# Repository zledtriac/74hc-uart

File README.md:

# 74hc-uart
In this project, you can find a schematics and descriptions for an asynchronous serial transmitter and receiver with 74hcxxx ICs. The circuits can be used for diy and old cpus where there is no support for UART, or you can just check the schematics to get an idea how an UART could be implemented in microcontrollers. It could be useful for VHDL designs.

## Transmitter
You can find the schematics and a detailed description of the serial transmitter in the ./hardware/transmitter folder.

## Receiver
Coming soon!

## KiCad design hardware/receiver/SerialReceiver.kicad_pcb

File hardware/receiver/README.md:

# Receiver
This is the receiver. It's only consists of 6 ICs. Actually 5 because U6 the 74HC244 IC can be left out, but with the current configuration it can 
be operated manually for demonstrations.

The receiver can receive a serial data transmission with **1 start bit, 8bit data without parity and 1 stop bit** on the end, with 9600 baude rate.

## Operation
The receiver has 3 pin headers for selecting the mode of operation (J4, J5, J6), before powering the receiver up, **please check the jumper positions, 
because the receiver can't operate in a circuit if the receiver is in manual operation mode.**

The receiver needs a 5V power supply to work, the power pins can be found on the Control header (J2) pin 1 - VCC, pin 2 - GND. After powering up the
receiver, due to the random behaviour of the U5A and U5B (74HC74) D flip-flops, it is possible that the cicuit will load a random data in the output 
register. It is recommanded to wait one full transmition time after power up and read the output register in order to clear the data ready signaling 
U5B D flip-flop.

The Control header (J2) has two other pins for control, pin 4 - !RD, and pin 7 - Ready. The !RD is an active-low input and this input enables the 
output shift register's tri-state output drivers so the received data will be present on the output.
The Ready is an output which will turns on when the data is received and ready to read.

When the RX input goes low, it will start the colock divider and if the input is held low for more than half the time of one bit then U5B (74HC74) 
D flip-flop will be set, and the Input trigger will lock on the signal and keeps the clock divider running. When the clock divider is running it means 
that the Bit counter and the Output shift register will receive a clock signal, and the data reception sequence is in progress. When the Q3 output on 
the Bit counter goes high, it will stops the Clock divider and the circuit will wait until the RX input goes back to high, and when the RX input went 
high it will resets the Input trigger and load the received data into the U4 (74HC595) output register and sets the U5A (74HC74) D flip-flop so the 
Ready output will turn to high.

The Output data register can be read at the same time when the data reception sequence is running because the output data register only updates when 
the data reception sequence is finished. But if the data is not readed befor the second reception finishes it will overwrite the data in the output 
register so the previous data will be lost.

## Manual operation
To use the circuit in a manual operation mode, set the jumper on the J5 pin header to enable the output of the U6 (74HC244) IC so the data on the 
output can be seen on the LED bar. If you want to use the button as a read signal then bridge the 1-2 pins on the J6 Mode select pin header. Or if you 
want to see the received data immediatelly, bridge the 3-4 pins in the J6 Mode select pin header.

## Oscillator
The oscillator is made out of two schmitt-triggered NAND gate of the U1 (74HC132) IC. With the 560pF C1 capacitor and the 10kOhm R1 plus the 10kOhm RV1 trimmer 
potentiometer this oscillator can be adjusted between 107kHz and 214kHz. The oscillator's frequency is not equal to the baud rate, because the sampling clock is
generated with the U2 (74HC191) counter IC which is in this case act as a clock divider. The Q3 output of the U2 (74HC191) IC will give a square wave signal with 
16th of the input frequency. So the equation for the baudrate is:
```
baud_rate = input_freq / 16
```
So the frequency of the oscillator should be 153.6kHz for a 9600 baud rate.\
For tuning the oscillator, a simple digital multimeter with frequency measuring capability is enough.

The J4 Clock select pin header can be used to fed external clock signal into the circuit. Just unplug the bridge from the 2-3 pins and connect the external clock 
signal the pin 3. The pin 4 can be used as a grounding point.

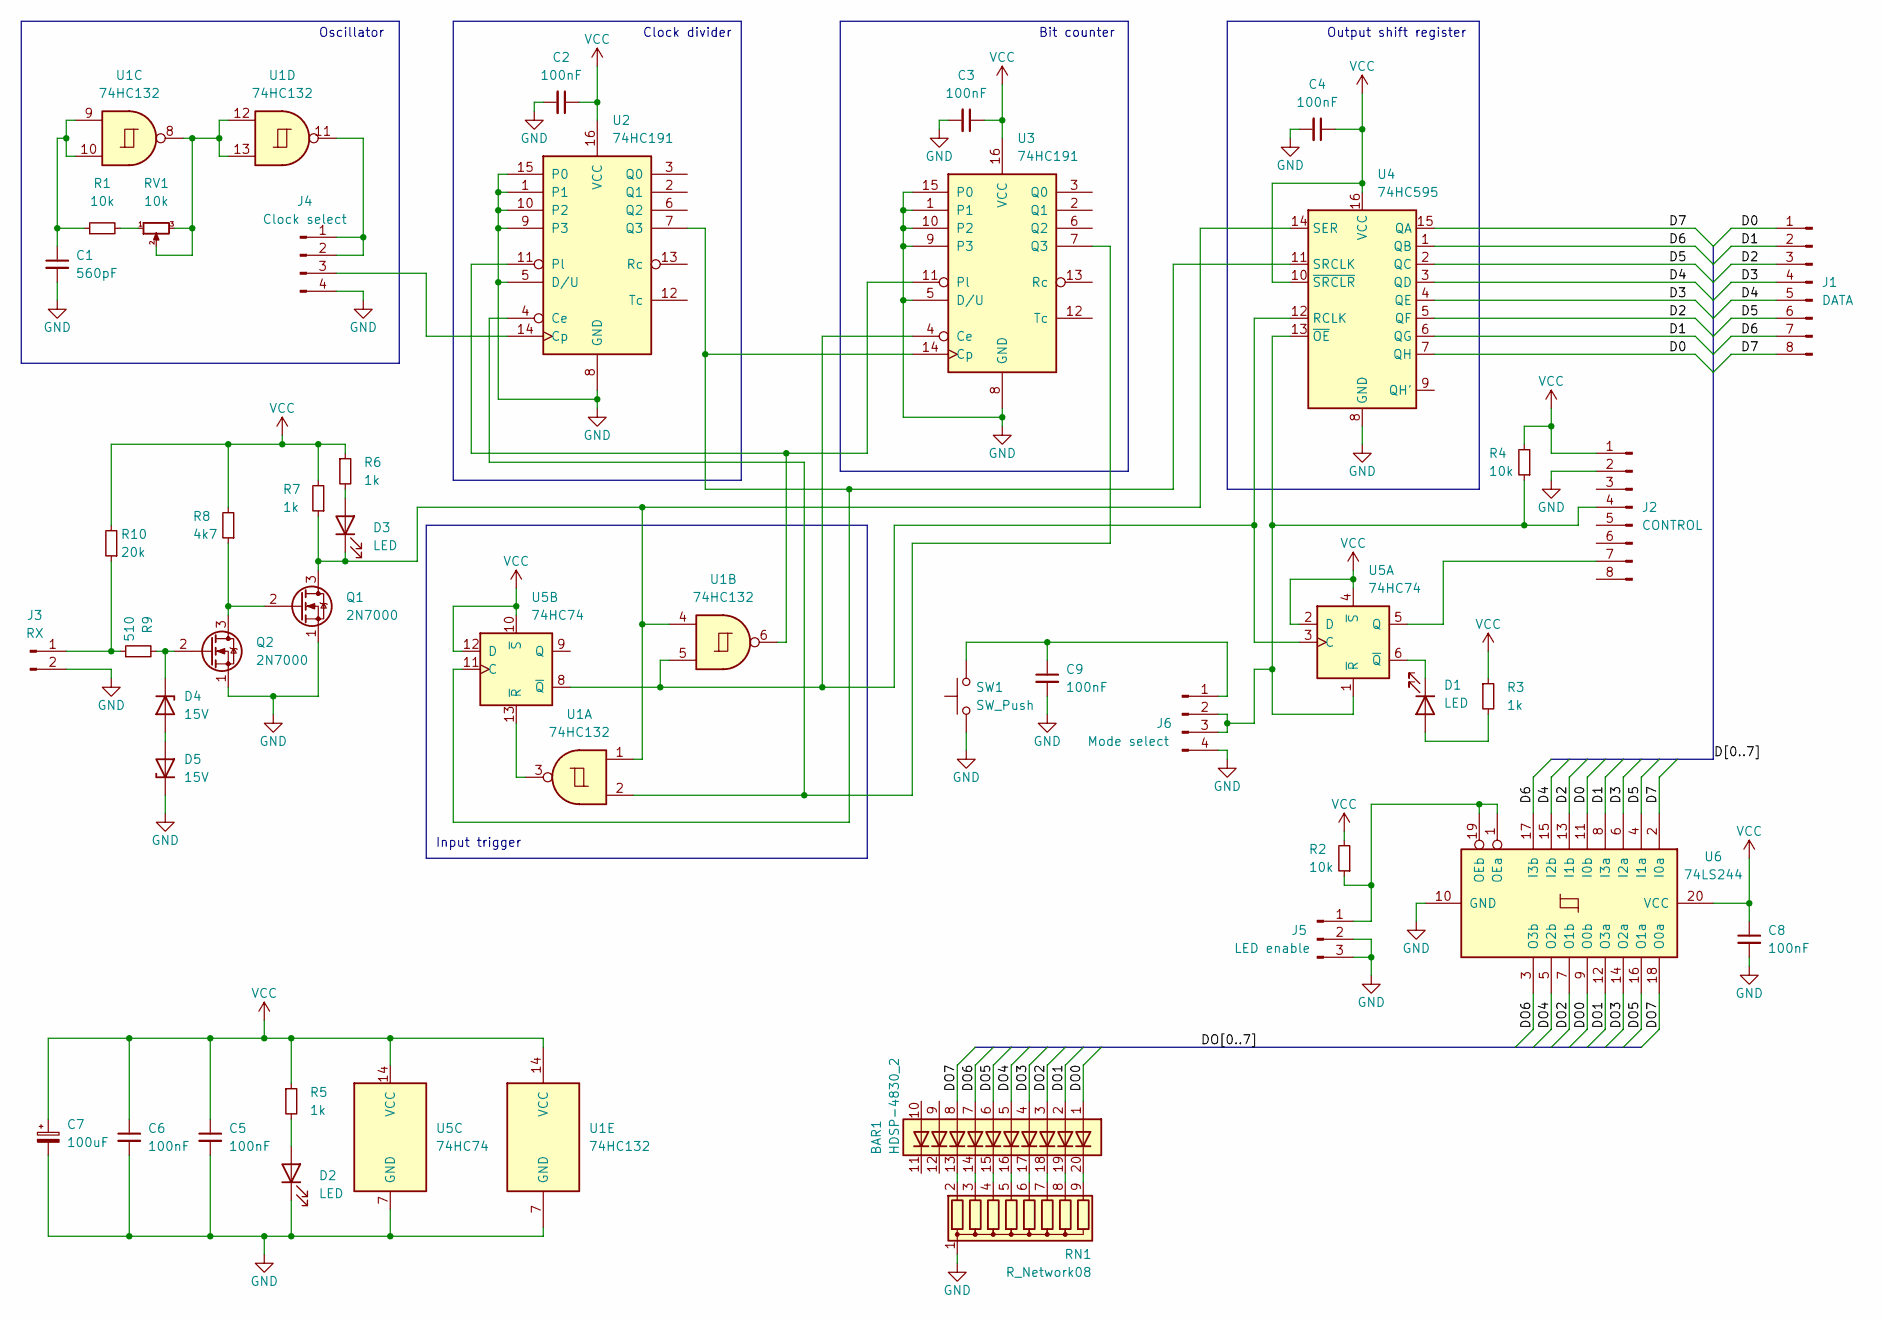
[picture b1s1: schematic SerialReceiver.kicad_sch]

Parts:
BAR1: HDSP-4830_2; DIP-20_W7.62mm_Socket
C1: 560pF; C_Disc_D3.0mm_W2.0mm_P2.50mm
C2, C3, C4, C5, C6, C8, C9: 100nF; C_Disc_D3.0mm_W2.0mm_P2.50mm
C7: 100uF; CP_Radial_D6.3mm_P2.50mm
D1, D2, D3: LED; LED_D3.0mm
D4, D5: 15V; D_DO-35_SOD27_P7.62mm_Horizontal
J1: DATA; PinHeader_1x08_P2.54mm_Horizontal
J2: CONTROL; PinHeader_1x08_P2.54mm_Horizontal
J3: RX; PinHeader_1x02_P2.54mm_Horizontal
J4: Clock select; PinHeader_1x04_P2.54mm_Vertical
J5: LED enable; PinHeader_1x03_P2.54mm_Vertical
J6: Mode select; PinHeader_1x04_P2.54mm_Vertical
Q1, Q2: 2N7000; TO-92_Inline_Wide
R1, R2, R4: 10k; R_Axial_DIN0207_L6.3mm_D2.5mm_P10.16mm_Horizontal
R3, R5, R6, R7: 1k; R_Axial_DIN0207_L6.3mm_D2.5mm_P10.16mm_Horizontal
R8: 4k7; R_Axial_DIN0207_L6.3mm_D2.5mm_P10.16mm_Horizontal
R9: 510; R_Axial_DIN0207_L6.3mm_D2.5mm_P10.16mm_Horizontal
R10: 20k; R_Axial_DIN0207_L6.3mm_D2.5mm_P10.16mm_Horizontal
RN1: R_Network08; R_Array_SIP9
RV1: 10k; Potentiometer_Bourns_3296W_Vertical
SW1: SW_Push; SW_PUSH_6mm
U1: 74HC132; DIP-14_W7.62mm
U2, U3: 74HC191; DIP-16_W7.62mm
U4: 74HC595; DIP-16_W7.62mm
U5: 74HC74; DIP-14_W7.62mm
U6: 74LS244; DIP-20_W7.62mm

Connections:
/D0: J1.1, U4.7 (QH), U6.11 (I0b)
/D1: J1.2, U4.6 (QG), U6.8 (I3a)
/D2: J1.3, U4.5 (QF), U6.13 (I1b)
/D3: J1.4, U4.4 (QE), U6.6 (I2a)
/D4: J1.5, U4.3 (QD), U6.15 (I2b)
/D5: J1.6, U4.2 (QC), U6.4 (I1a)
/D6: J1.7, U4.1 (QB), U6.17 (I3b)
/D7: J1.8, U4.15 (QA), U6.2 (I0a)
/DO0: BAR1.1 (A), U6.9 (O0b)
/DO1: BAR1.2 (A), U6.12 (O3a)
/DO2: BAR1.3 (A), U6.7 (O1b)
/DO3: BAR1.4 (A), U6.14 (O2a)
/DO4: BAR1.5 (A), U6.5 (O2b)
/DO5: BAR1.6 (A), U6.16 (O1a)
/DO6: BAR1.7 (A), U6.3 (O3b)
/DO7: BAR1.8 (A), U6.18 (O0a)
GND: C1.2, C2.2, C3.2, C4.2, C5.2, C6.2, C7.2, C8.2, C9.2, D2.1 (K), D5.1 (K), J2.2, J3.2, J4.4, J5.2, J5.3, J6.4, Q1.1 (S), Q2.1 (S), RN1.1 (common), SW1.1, U1.7 (GND), U2.1, U2.5 (D/U), U2.8 (GND), U2.9 (P3), U2.10 (P2), U2.15 (P0), U3.1, U3.5 (D/U), U3.8 (GND), U3.9 (P3), U3.10 (P2), U3.15 (P0), U4.8 (GND), U5.7 (GND), U6.10 (GND)
unnamed: BAR1.13 (K), RN1.2 (R1)
unnamed: BAR1.14 (K), RN1.3 (R2)
unnamed: BAR1.15 (K), RN1.4 (R3)
unnamed: BAR1.16 (K), RN1.5 (R4)
unnamed: BAR1.17 (K), RN1.6 (R5)
unnamed: BAR1.18 (K), RN1.7 (R6)
unnamed: BAR1.19 (K), RN1.8 (R7)
unnamed: BAR1.20 (K), RN1.9 (R8)
unnamed: C1.1, R1.1, U1.9, U1.10
unnamed: C9.1, J6.1, SW1.2
unnamed: D1.1 (K), U5.6 (~Q)
unnamed: D1.2 (A), R3.2
unnamed: D2.2 (A), R5.2
unnamed: D3.1 (K), Q1.3 (D), R7.1, U1.1, U1.4, U4.14 (SER)
unnamed: D3.2 (A), R6.2
unnamed: D4.1 (K), Q2.2 (G), R9.2
unnamed: D4.2 (A), D5.2 (A)
unnamed: J2.4, J6.2, J6.3, R4.1, U4.13 (~OE), U5.1 (~R)
unnamed: J2.7, U5.5 (Q)
unnamed: J3.1, R9.1, R10.1
unnamed: J4.1, J4.2, U1.11
unnamed: J4.3, U2.14 (Cp)
unnamed: J5.1, R2.1, U6.1 (OEa), U6.19 (OEb)
unnamed: Q1.2 (G), Q2.3 (D), R8.1
unnamed: R1.2, RV1.1
unnamed: U1.2, U2.4 (Ce), U3.7 (Q3)
unnamed: U1.3, U5.13 (~R)
unnamed: U1.5, U3.4 (Ce), U4.12 (RCLK), U5.3 (C), U5.8 (~Q)
unnamed: U1.6, U2.11 (Pl), U3.11 (Pl)
unnamed: RV1.2, RV1.3, U1.8, U1.12, U1.13
unnamed: U2.7 (Q3), U3.14 (Cp), U4.11 (SRCLK), U5.11 (C)
VCC: C2.1, C3.1, C4.1, C5.1, C6.1, C7.1, C8.1, J2.1, R2.2, R3.1, R4.2, R5.1, R6.1, R7.2, R8.2, R10.2, U1.14 (VCC), U2.16 (VCC), U3.16 (VCC), U4.10 (~SRCLR), U4.16 (VCC), U5.2 (D), U5.4 (~S), U5.10 (~S), U5.12 (D), U5.14 (VCC), U6.20 (VCC)

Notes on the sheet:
Bit counter
Clock divider
Oscillator
Output shift register
Input trigger

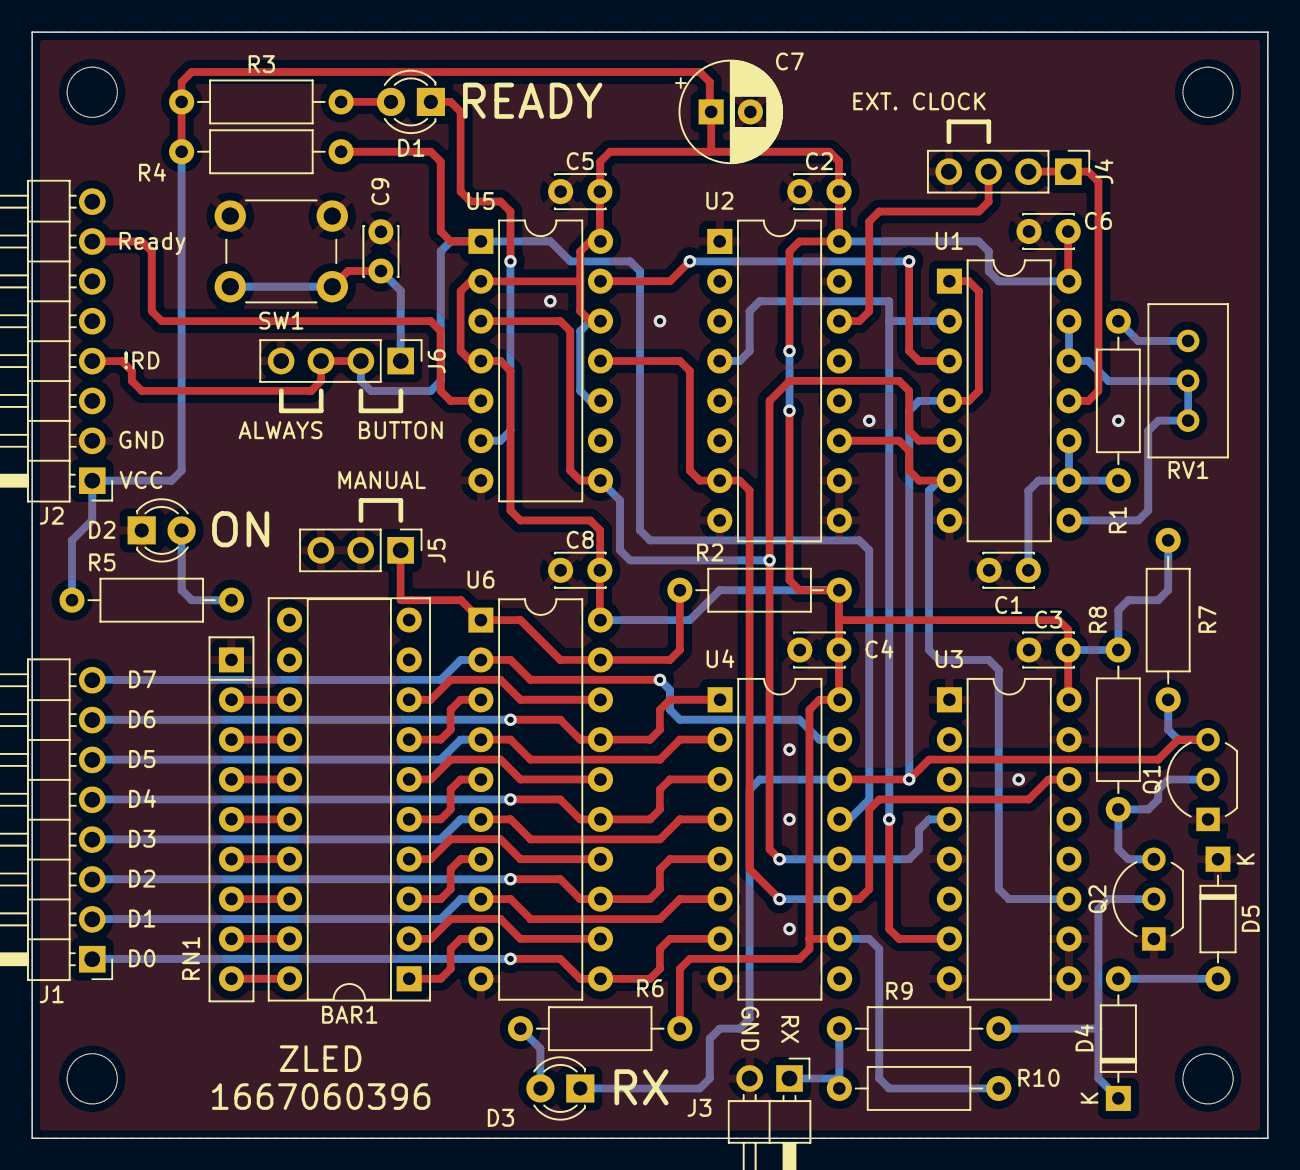
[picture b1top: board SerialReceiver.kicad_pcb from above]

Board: 2 copper layers, 78.7 x 70.5 mm, 42 parts (0 on the bottom side), 49 nets.

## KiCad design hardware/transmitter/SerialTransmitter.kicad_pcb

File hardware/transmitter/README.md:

# Transmitter
This is the transmitter. It's only consists of 6 ICs. Actually 5 because U6 the 74HC244 IC can be left out, but with the current configuration it can 
be operated manually for demonstrations.

The transmitter transmits the data with **1 start bit, 8bit data without parity and 1 stop bit** on the end, with 9600 baud rate.

## Operation
The transmitter has 3 pin headers for selecting the mode of operation (J3, J5, J6), before powering the transmitter up, **please check the jumper positions, 
because the transmitter can't operate in a circuit if the transmitter is in manual operation mode.**

The transmitter needs a 5V power supply to work, the power pins can be found on the Control header (J4) pin 1 - VCC, pin 2 - GND. After powering up the
transmitter, due to the random behaviour of the set-reset latch made with the U5D and U5C NAND gate (74HC132) and of the U3A and U3B (74HC74) D flip-flops, 
it is possible that the cicuit will transmit a random data on the output.

*If this behaviour can cause issues in the target device, it is recommended to build
an output enable circuit after the U3B pin 9 output, which can be controlled by a switch, delay circuit or from software if the transmitter is connected to a CPU.*

The Control header (J4) has two other pins for control, pin 5 - !WR, and pin 8 - Busy. The !WR is an active-low input and this input starts the data transmission.
The Busy is an output which will be held high while the transmission is going (Short pulse section on *Figure 1.*), or while the !WR input is held low (Long pulse section on *Figure 1.*).

To send data, first set the data on the Data header (J1) then send a low pulse on the !WR pin. This will trigger the Input trigger circuitry. In this stage the output 
of the U5D will turn high, but since the U3A D flip-flop is not set, the inverted output of the U3A D flip-flop is also high, this will set the output of the U4A NAND 
gate to low, this will enables the load pins of the U1 (74HC165) shift register and the U2 (74HC191) counter IC, so the data will be loaded into the U1 shift register 
and the U2 counter IC will be set to 0. There is an extra bit made by the U4B NAND gate and the U3B D flip-flop, in the loading process it will set to one, this extra 
bit is the START bit. Since the U3A D flip-flop's clock input is connected to the main clock signal, the U3A D flip-flop will set and the inverted output of the U3A D 
flip-flop will turn to low.
After this, every clock pulse will shift out the data from U1 (74HC165) shift register, and increment the U2 (74HC191) counter until U2 (74HC191) counter reaches 8.
When the U2 (74HC191) counter reaches 8, the counting will stop and if the !WR input is high, it will reset the Input trigger circuitry, and after this, one clock 
pulse is needed to reset the U3A D flip-flop. So when the next write pulse comes in, the whole process will repeat.

## Manual operation
To use the circuit in a manual operation mode, set the jumper on the J3 pin header to bridge the 1-2 pins, and on the J5 pin header to bridge the 2-3 pins. This will 
enables the U6 (74HC244) output so the data set by the SW1 dip switch will be put on the DATA input, and it will connect the SW2 button to the !WR input.
After the data set on the SW1 dip switch, the data sending can be initiated by pressing the SW2 button.

**please note that if the circuit is in manual operation mode, the DATA input will be driven by the U6 (74HC244) output and the !WR input will connected to the SW2 
button, so it can't be used in other circuits!**

## Oscillator
The oscillator is made out of two schmitt-triggered NAND gate of the U4 (74HC132) IC. With the 10nF C7 capacitor and the 10kOhm R5 plus the 10kOhm RV1 trimmer 
potentiometer this oscillator can be adjusted between 6kHz and 12kHz. The oscillator's frequency is equal to the baud rate, so for the 9600 baud rate set the 
oscillator to 9.6kHz. For the tuning, a simple digital multimeter with frequency measuring capability is enough.

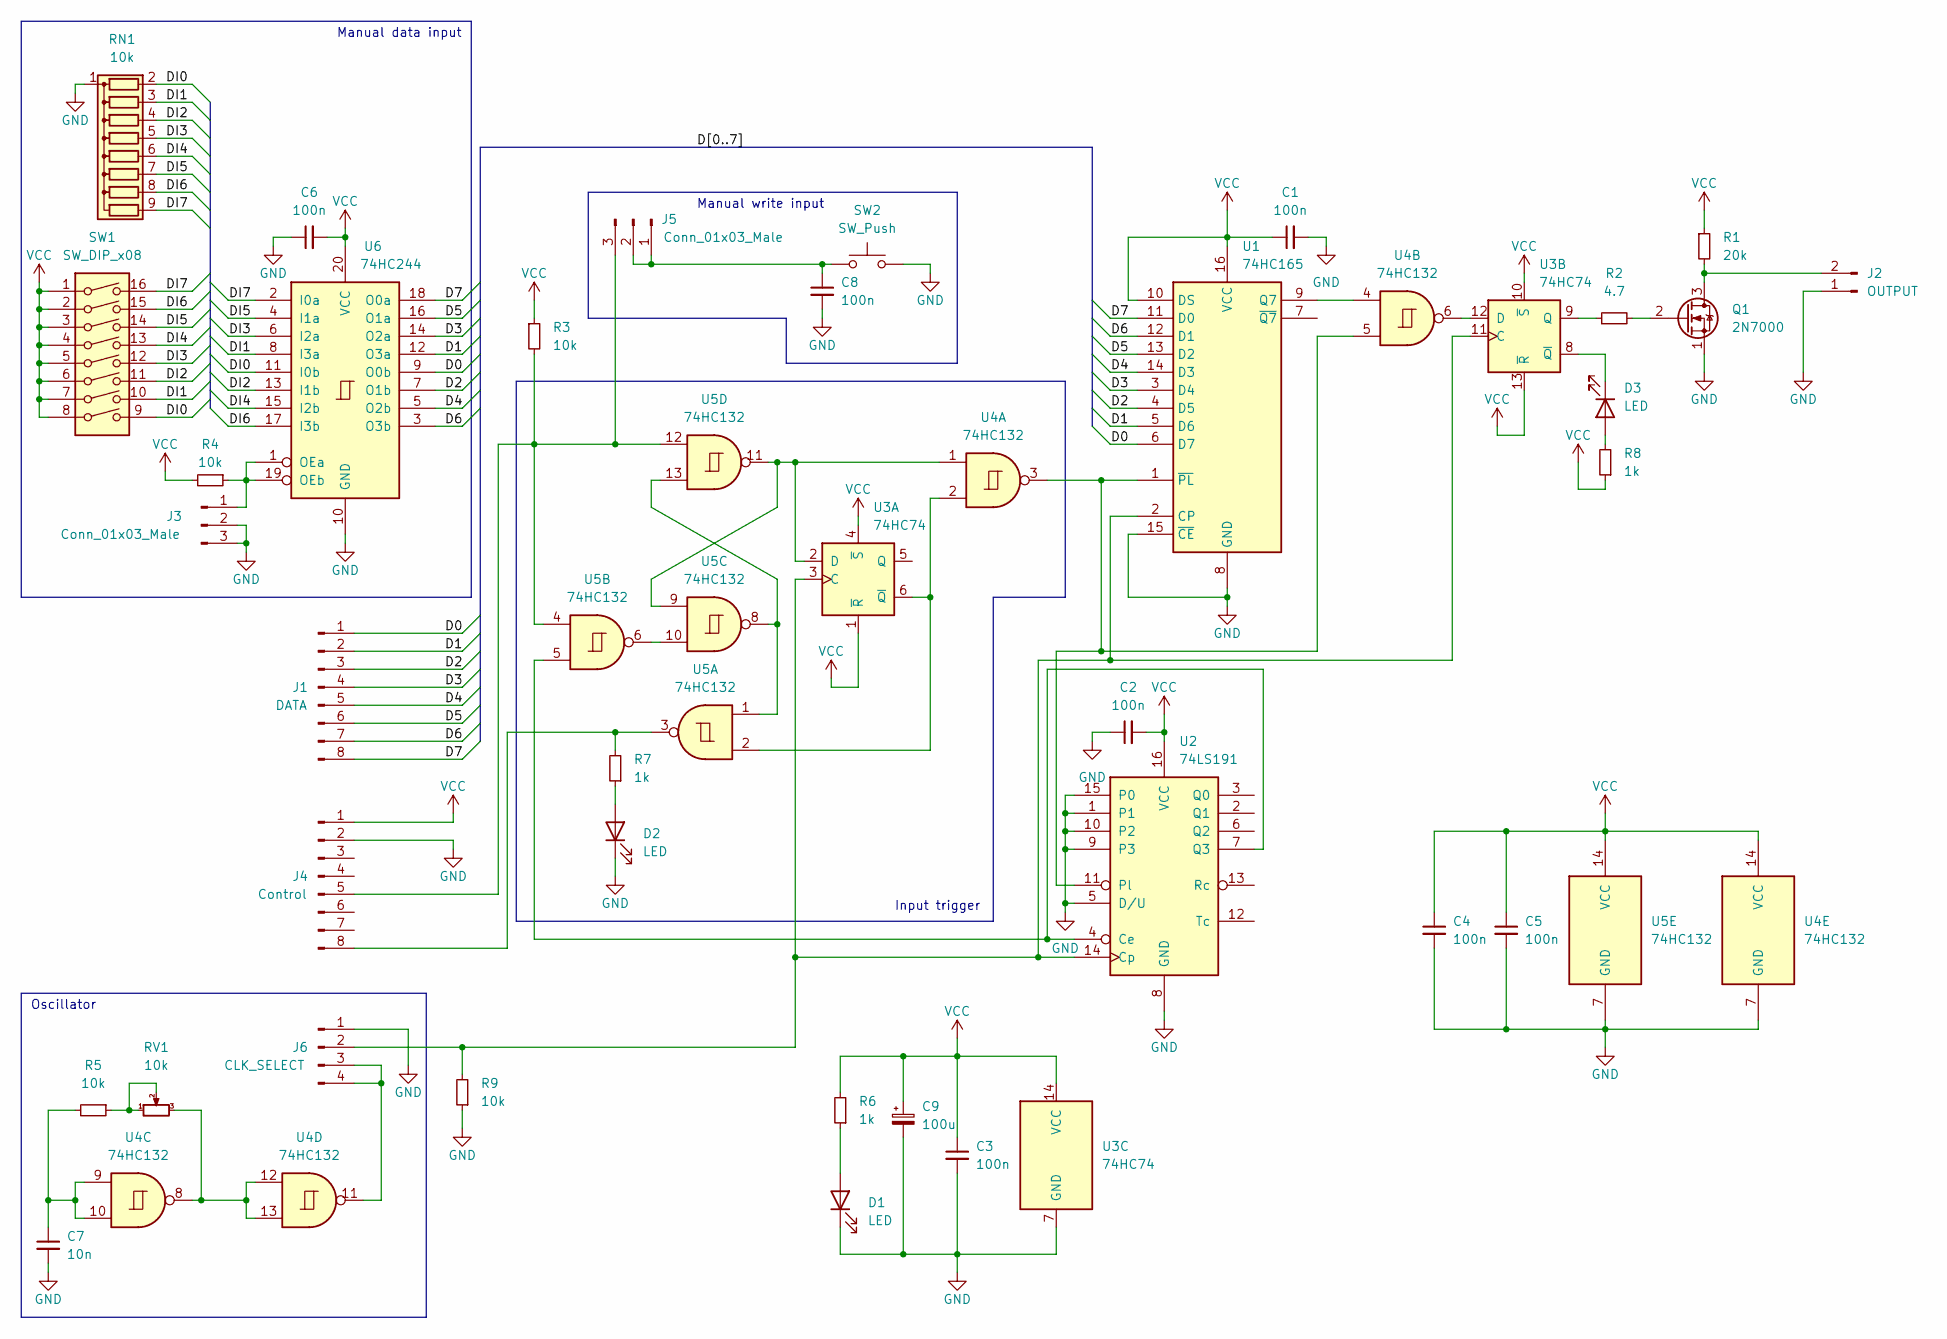
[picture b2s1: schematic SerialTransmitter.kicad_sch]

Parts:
C1, C2, C3, C4, C5, C6, C8: 100n; C_Disc_D3.0mm_W2.0mm_P2.50mm
C7: 10n; C_Disc_D3.0mm_W2.0mm_P2.50mm
C9: 100u; CP_Radial_D6.3mm_P2.50mm
D1, D2, D3: LED; LED_D3.0mm
J1: DATA; PinHeader_1x08_P2.54mm_Horizontal
J2: OUTPUT; PinHeader_1x02_P2.54mm_Horizontal
J3, J5: Conn_01x03_Male; PinHeader_1x03_P2.54mm_Vertical
J4: Control; PinHeader_1x08_P2.54mm_Horizontal
J6: CLK_SELECT; PinHeader_1x04_P2.54mm_Vertical
Q1: 2N7000; TO-92_Inline
R1: 20k; R_Axial_DIN0207_L6.3mm_D2.5mm_P10.16mm_Horizontal
R2: 4.7; R_Axial_DIN0207_L6.3mm_D2.5mm_P10.16mm_Horizontal
R3, R4, R5, R9: 10k; R_Axial_DIN0207_L6.3mm_D2.5mm_P10.16mm_Horizontal
R6, R7, R8: 1k; R_Axial_DIN0207_L6.3mm_D2.5mm_P10.16mm_Horizontal
RN1: 10k; R_Array_SIP9
RV1: 10k; Potentiometer_Bourns_3296W_Vertical
SW1: SW_DIP_x08; DIP-16_W7.62mm_Socket
SW2: SW_Push; SW_PUSH_6mm
U1: 74HC165; DIP-16_W7.62mm
U2: 74LS191; DIP-16_W7.62mm
U3: 74HC74; DIP-14_W7.62mm
U4, U5: 74HC132; DIP-14_W7.62mm
U6: 74HC244; DIP-20_W7.62mm

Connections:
/D0: J1.1, U1.6 (D7), U6.9 (O0b)
/D1: J1.2, U1.5 (D6), U6.12 (O3a)
/D2: J1.3, U1.4 (D5), U6.7 (O1b)
/D3: J1.4, U1.3 (D4), U6.14 (O2a)
/D4: J1.5, U1.14 (D3), U6.5 (O2b)
/D5: J1.6, U1.13 (D2), U6.16 (O1a)
/D6: J1.7, U1.12 (D1), U6.3 (O3b)
/D7: J1.8, U1.11 (D0), U6.18 (O0a)
/DI0: RN1.2 (R1), SW1.9, U6.11 (I0b)
/DI1: RN1.3 (R2), SW1.10, U6.8 (I3a)
/DI2: RN1.4 (R3), SW1.11, U6.13 (I1b)
/DI3: RN1.5 (R4), SW1.12, U6.6 (I2a)
/DI4: RN1.6 (R5), SW1.13, U6.15 (I2b)
/DI5: RN1.7 (R6), SW1.14, U6.4 (I1a)
/DI6: RN1.8 (R7), SW1.15, U6.17 (I3b)
/DI7: RN1.9 (R8), SW1.16, U6.2 (I0a)
unnamed: C7.1, R5.2, U4.9, U4.10
unnamed: C8.1, J5.1, J5.2, SW2.1
unnamed: D1.2 (A), R6.1
unnamed: D2.2 (A), R7.1
unnamed: D3.1 (K), U3.8 (~Q)
unnamed: D3.2 (A), R8.2
unnamed: J2.2, Q1.3 (D), R1.2
unnamed: J3.1, R4.1, U6.1 (OEa), U6.19 (OEb)
unnamed: J4.5, J5.3, R3.2, U5.4, U5.12
unnamed: J6.2, R9.2, U1.2 (CP), U2.14 (Cp), U3.3 (C), U3.11 (C)
unnamed: J6.3, J6.4, U4.11
unnamed: Q1.2 (G), R2.2
unnamed: R2.1, U3.9 (Q)
unnamed: R5.1, RV1.1, RV1.2
unnamed: J4.8, R7.2, U5.3
unnamed: RV1.3, U4.8, U4.12, U4.13
unnamed: U1.1 (~PL), U2.11 (Pl), U4.3, U4.5
unnamed: U1.9 (Q7), U4.4
unnamed: U2.4 (Ce), U2.7 (Q3), U5.5
unnamed: U3.2 (D), U4.1, U5.9, U5.11
unnamed: U3.6 (~Q), U4.2, U5.2
unnamed: U3.12 (D), U4.6
unnamed: U5.1, U5.8, U5.13
unnamed: U5.6, U5.10

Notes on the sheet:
Input trigger
Oscillator
Manual data input
Manual write input

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
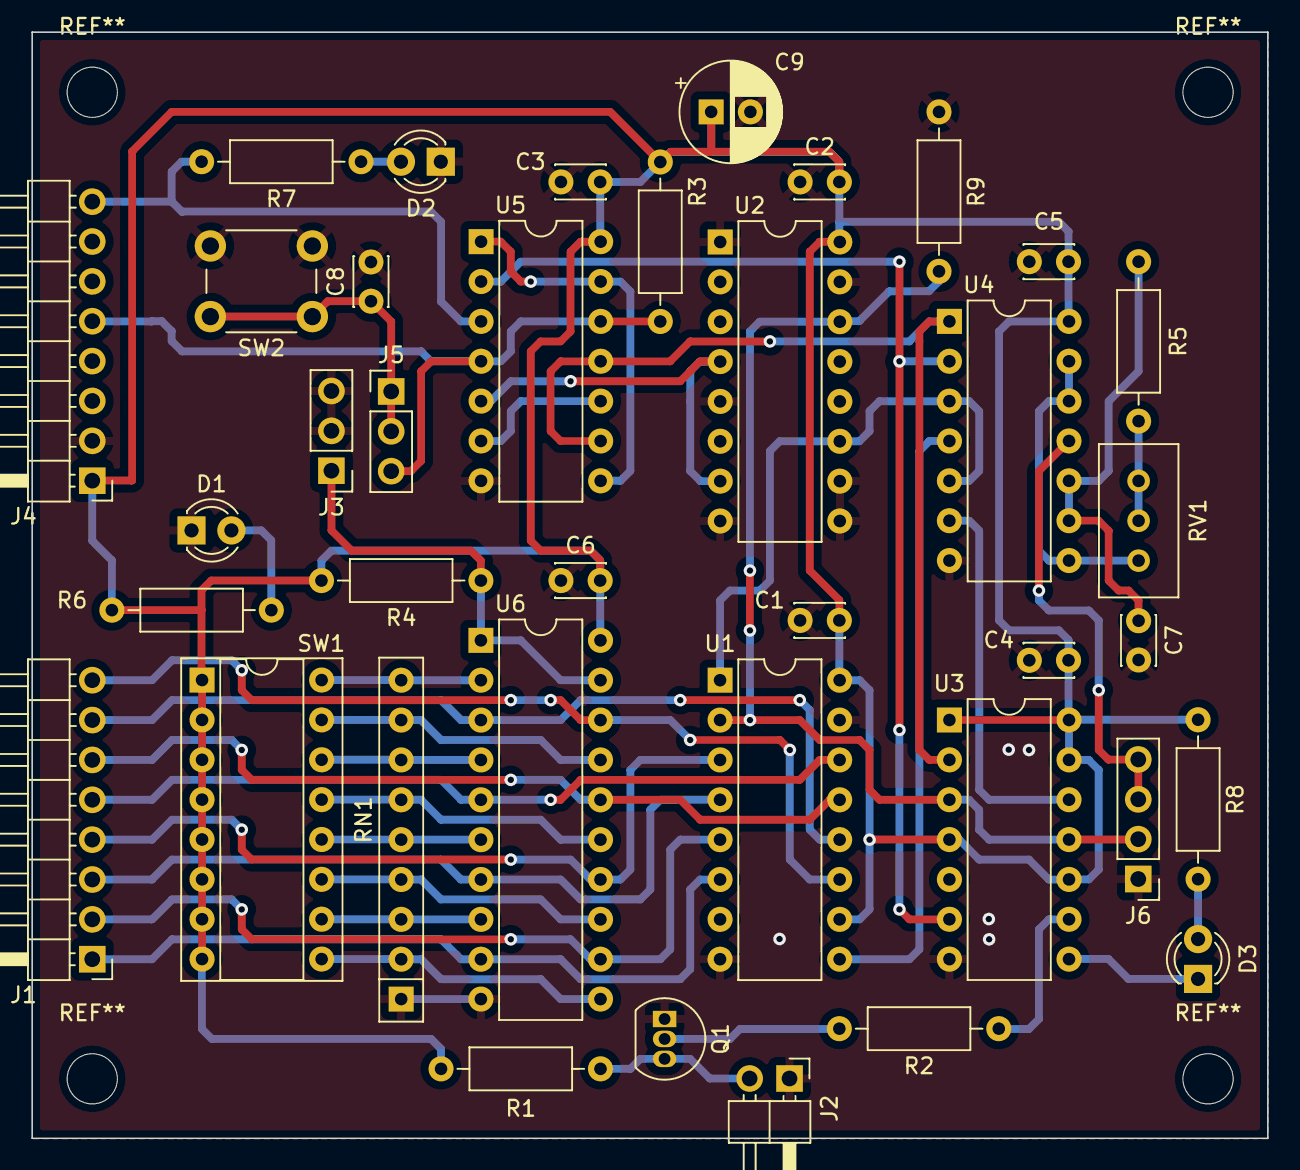
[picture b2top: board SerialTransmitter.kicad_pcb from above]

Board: 2 copper layers, 78.7 x 70.5 mm, 38 parts (0 on the bottom side), 42 nets.

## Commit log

2022-08-24 Upload project files.
2022-09-03 Added the receiver project files.
2022-09-03 Added some notes to the schematic, changed the names of the components, moved some parts.
2022-09-18 Description update.
2022-09-26 The schematic has been exported to PDFs, and added timing diagram files.
2022-09-26 Update Description.
2022-09-27 Continued the design of the receiver.
2022-09-28 Setting the names and the values of the receiver's components.
2022-10-02 Starting the PCB design.
2022-10-04 Changed the layout of the schematic for better wiring.
2022-10-23 Made an RX input protection, and almost finished the PCB.
2022-10-23 Input protection is now on the PCB.
2022-10-23 The receiver's PCB is finished.
2022-10-26 The schematic and the PCB is finished.
2022-10-29 Minor fixes on the receiver's PCB.
2022-12-13 Create README.md
    A README.dm file is created for the receiver.
2022-12-16 Exported the Schematics to PDF for the receiver.
2023-01-12 Updated the receiver's readme.
